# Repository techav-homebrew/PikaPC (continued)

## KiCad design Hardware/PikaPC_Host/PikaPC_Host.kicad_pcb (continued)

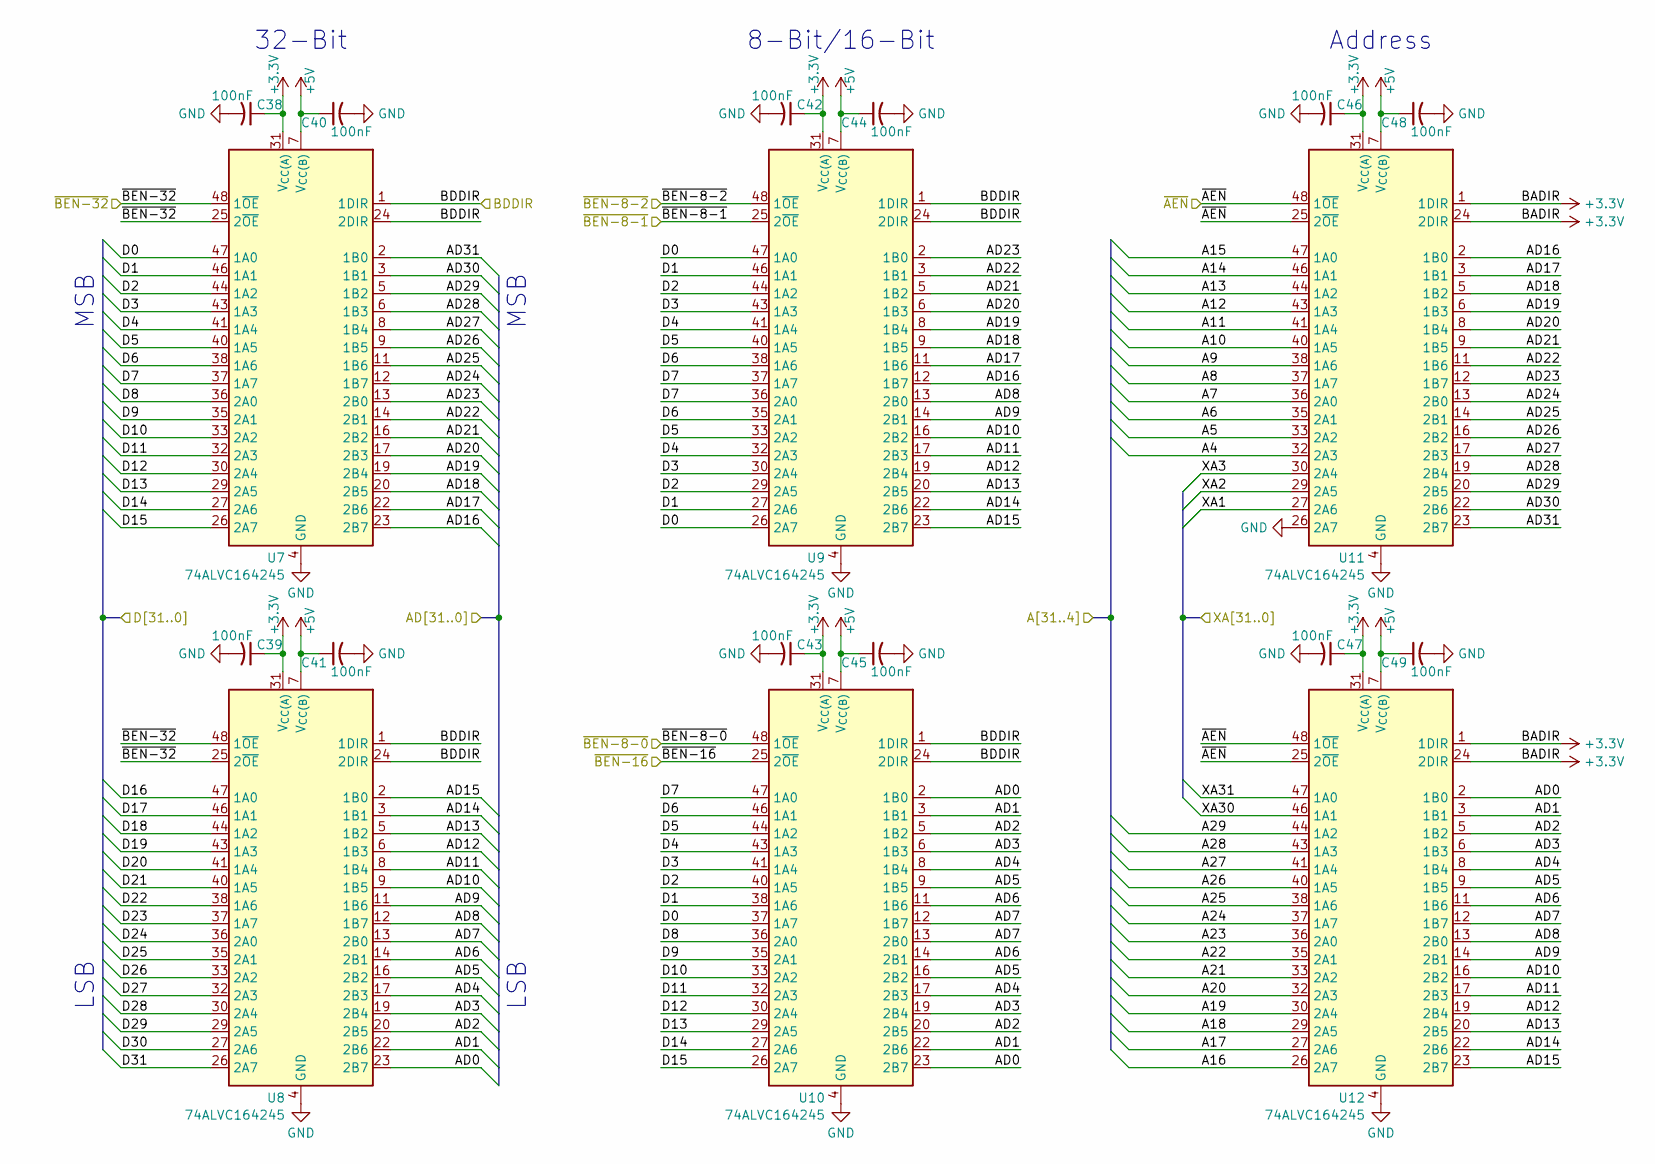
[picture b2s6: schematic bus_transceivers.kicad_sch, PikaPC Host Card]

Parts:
C38, C39, C40, C41, C42, C43, C44, C45, C46, C47, C48, C49: 100nF; C_0805_2012Metric; Mouser 187-CL21B104KACNNNC
U7, U8, U9, U10, U11, U12: 74ALVC164245; TSSOP-48_6.1x12.5mm_P0.5mm; Mouser 972-74ALVC164245PAG8

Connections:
+3.3V: C38.1, C39.1, C42.1, C43.1, C46.1, C47.1, U7.31 (V_{CC(A)}), U7.42 (V_{CC(A)}), U8.31 (V_{CC(A)}), U8.42 (V_{CC(A)}), U9.31 (V_{CC(A)}), U9.42 (V_{CC(A)}), U10.31 (V_{CC(A)}), U10.42 (V_{CC(A)}), U11.1 (1DIR), U11.24 (2DIR), U11.31 (V_{CC(A)}), U11.42 (V_{CC(A)}), U12.1 (1DIR), U12.24 (2DIR), U12.31 (V_{CC(A)}), U12.42 (V_{CC(A)}); also elsewhere on the board
+5V: C40.1, C41.1, C44.1, C45.1, C48.1, C49.1, U7.7 (V_{CC(B)}), U7.18 (V_{CC(B)}), U8.7 (V_{CC(B)}), U8.18 (V_{CC(B)}), U9.7 (V_{CC(B)}), U9.18 (V_{CC(B)}), U10.7 (V_{CC(B)}), U10.18 (V_{CC(B)}), U11.7 (V_{CC(B)}), U11.18 (V_{CC(B)}), U12.7 (V_{CC(B)}), U12.18 (V_{CC(B)}); also elsewhere on the board
/CPU Bus/D0: U7.47 (1A0), U9.26 (2A7), U9.47 (1A0), U10.37 (1A7); also elsewhere on the board
/CPU Bus/D1: U7.46 (1A1), U9.27 (2A6), U9.46 (1A1), U10.38 (1A6); also elsewhere on the board
/CPU Bus/D2: U7.44 (1A2), U9.29 (2A5), U9.44 (1A2), U10.40 (1A5); also elsewhere on the board
/CPU Bus/D3: U7.43 (1A3), U9.30 (2A4), U9.43 (1A3), U10.41 (1A4); also elsewhere on the board
/CPU Bus/D4: U7.41 (1A4), U9.32 (2A3), U9.41 (1A4), U10.43 (1A3); also elsewhere on the board
/CPU Bus/D5: U7.40 (1A5), U9.33 (2A2), U9.40 (1A5), U10.44 (1A2); also elsewhere on the board
/CPU Bus/D6: U7.38 (1A6), U9.35 (2A1), U9.38 (1A6), U10.46 (1A1); also elsewhere on the board
/CPU Bus/D7: U7.37 (1A7), U9.36 (2A0), U9.37 (1A7), U10.47 (1A0); also elsewhere on the board
/CPU Bus/D8: U7.36 (2A0), U10.36 (2A0); also elsewhere on the board
/CPU Bus/D9: U7.35 (2A1), U10.35 (2A1); also elsewhere on the board
/CPU Bus/D10: U7.33 (2A2), U10.33 (2A2); also elsewhere on the board
/CPU Bus/D11: U7.32 (2A3), U10.32 (2A3); also elsewhere on the board
/CPU Bus/D12: U7.30 (2A4), U10.30 (2A4); also elsewhere on the board
/CPU Bus/D13: U7.29 (2A5), U10.29 (2A5); also elsewhere on the board
/CPU Bus/D14: U7.27 (2A6), U10.27 (2A6); also elsewhere on the board
/CPU Bus/D15: U7.26 (2A7), U10.26 (2A7); also elsewhere on the board
/CPU Bus/D16: U8.47 (1A0); also elsewhere on the board
/CPU Bus/D17: U8.46 (1A1); also elsewhere on the board
/CPU Bus/D18: U8.44 (1A2); also elsewhere on the board
/CPU Bus/D19: U8.43 (1A3); also elsewhere on the board
/CPU Bus/D20: U8.41 (1A4); also elsewhere on the board
/CPU Bus/D21: U8.40 (1A5); also elsewhere on the board
/CPU Bus/D22: U8.38 (1A6); also elsewhere on the board
/CPU Bus/D23: U8.37 (1A7); also elsewhere on the board
/CPU Bus/D24: U8.36 (2A0); also elsewhere on the board
/CPU Bus/D25: U8.35 (2A1); also elsewhere on the board
/CPU Bus/D26: U8.33 (2A2); also elsewhere on the board
/CPU Bus/D27: U8.32 (2A3); also elsewhere on the board
/CPU Bus/D28: U8.30 (2A4); also elsewhere on the board
/CPU Bus/D29: U8.29 (2A5); also elsewhere on the board
/CPU Bus/D30: U8.27 (2A6); also elsewhere on the board
/CPU Bus/D31: U8.26 (2A7); also elsewhere on the board
/Main Bus/A6: U11.35 (2A1); also elsewhere on the board
/Main Bus/A7: U11.36 (2A0); also elsewhere on the board
/Main Bus/A8: U11.37 (1A7); also elsewhere on the board
/Main Bus/A9: U11.38 (1A6); also elsewhere on the board
/Main Bus/A10: U11.40 (1A5); also elsewhere on the board
/Main Bus/A11: U11.41 (1A4); also elsewhere on the board
/Main Bus/A12: U11.43 (1A3); also elsewhere on the board
/Main Bus/A13: U11.44 (1A2); also elsewhere on the board
/Main Bus/A14: U11.46 (1A1); also elsewhere on the board
/Main Bus/A15: U11.47 (1A0); also elsewhere on the board
/Main Bus/A16: U12.26 (2A7); also elsewhere on the board
/Main Bus/A17: U12.27 (2A6); also elsewhere on the board
/Main Bus/A18: U12.29 (2A5); also elsewhere on the board
/Main Bus/A19: U12.30 (2A4); also elsewhere on the board
/Main Bus/A20: U12.32 (2A3); also elsewhere on the board
/Main Bus/A21: U12.33 (2A2); also elsewhere on the board
/Main Bus/A22: U12.35 (2A1); also elsewhere on the board
/Main Bus/A23: U12.36 (2A0); also elsewhere on the board
/Main Bus/A24: U12.37 (1A7); also elsewhere on the board
/Main Bus/A25: U12.38 (1A6); also elsewhere on the board
/Main Bus/A26: U12.40 (1A5); also elsewhere on the board
/Main Bus/A27: U12.41 (1A4); also elsewhere on the board
/Main Bus/A28: U12.43 (1A3); also elsewhere on the board
/Main Bus/A29: U12.44 (1A2); also elsewhere on the board
/Main Bus/AD0: U8.23 (2B7), U10.2 (1B0), U10.23 (2B7), U12.2 (1B0); also elsewhere on the board
/Main Bus/AD1: U8.22 (2B6), U10.3 (1B1), U10.22 (2B6), U12.3 (1B1); also elsewhere on the board
/Main Bus/AD2: U8.20 (2B5), U10.5 (1B2), U10.20 (2B5), U12.5 (1B2); also elsewhere on the board
/Main Bus/AD3: U8.19 (2B4), U10.6 (1B3), U10.19 (2B4), U12.6 (1B3); also elsewhere on the board
/Main Bus/AD4: U8.17 (2B3), U10.8 (1B4), U10.17 (2B3), U12.8 (1B4); also elsewhere on the board
/Main Bus/AD5: U8.16 (2B2), U10.9 (1B5), U10.16 (2B2), U12.9 (1B5); also elsewhere on the board
/Main Bus/AD6: U8.14 (2B1), U10.11 (1B6), U10.14 (2B1), U12.11 (1B6); also elsewhere on the board
/Main Bus/AD7: U8.13 (2B0), U10.12 (1B7), U10.13 (2B0), U12.12 (1B7); also elsewhere on the board
/Main Bus/AD8: U8.12 (1B7), U9.13 (2B0), U12.13 (2B0); also elsewhere on the board
/Main Bus/AD9: U8.11 (1B6), U9.14 (2B1), U12.14 (2B1); also elsewhere on the board
/Main Bus/AD10: U8.9 (1B5), U9.16 (2B2), U12.16 (2B2); also elsewhere on the board
/Main Bus/AD11: U8.8 (1B4), U9.17 (2B3), U12.17 (2B3); also elsewhere on the board
/Main Bus/AD12: U8.6 (1B3), U9.19 (2B4), U12.19 (2B4); also elsewhere on the board
/Main Bus/AD13: U8.5 (1B2), U9.20 (2B5), U12.20 (2B5); also elsewhere on the board
/Main Bus/AD14: U8.3 (1B1), U9.22 (2B6), U12.22 (2B6); also elsewhere on the board
/Main Bus/AD15: U8.2 (1B0), U9.23 (2B7), U12.23 (2B7); also elsewhere on the board
/Main Bus/AD16: U7.23 (2B7), U9.12 (1B7), U11.2 (1B0); also elsewhere on the board
/Main Bus/AD17: U7.22 (2B6), U9.11 (1B6), U11.3 (1B1); also elsewhere on the board
/Main Bus/AD18: U7.20 (2B5), U9.9 (1B5), U11.5 (1B2); also elsewhere on the board
/Main Bus/AD19: U7.19 (2B4), U9.8 (1B4), U11.6 (1B3); also elsewhere on the board
/Main Bus/AD20: U7.17 (2B3), U9.6 (1B3), U11.8 (1B4); also elsewhere on the board
/Main Bus/AD21: U7.16 (2B2), U9.5 (1B2), U11.9 (1B5); also elsewhere on the board
/Main Bus/AD22: U7.14 (2B1), U9.3 (1B1), U11.11 (1B6); also elsewhere on the board
/Main Bus/AD23: U7.13 (2B0), U9.2 (1B0), U11.12 (1B7); also elsewhere on the board
/Main Bus/AD24: U7.12 (1B7), U11.13 (2B0); also elsewhere on the board
/Main Bus/AD25: U7.11 (1B6), U11.14 (2B1); also elsewhere on the board
/Main Bus/AD26: U7.9 (1B5), U11.16 (2B2); also elsewhere on the board
/Main Bus/AD27: U7.8 (1B4), U11.17 (2B3); also elsewhere on the board
/Main Bus/AD28: U7.6 (1B3), U11.19 (2B4); also elsewhere on the board
/Main Bus/AD29: U7.5 (1B2), U11.20 (2B5); also elsewhere on the board
/Main Bus/AD30: U7.3 (1B1), U11.22 (2B6); also elsewhere on the board
/Main Bus/AD31: U7.2 (1B0), U11.23 (2B7); also elsewhere on the board
/Main Bus/BDDIR: U7.1 (1DIR), U7.24 (2DIR), U8.1 (1DIR), U8.24 (2DIR), U9.1 (1DIR), U9.24 (2DIR), U10.1 (1DIR), U10.24 (2DIR); also elsewhere on the board
/Main Bus/XA1: U11.27 (2A6); also elsewhere on the board
/Main Bus/XA2: U11.29 (2A5); also elsewhere on the board
/Main Bus/XA3: U11.30 (2A4); also elsewhere on the board
/Main Bus/XA30: U12.46 (1A1); also elsewhere on the board
/Main Bus/XA31: U12.47 (1A0); also elsewhere on the board
/Main Bus/~AEN: U11.25 (2~OE), U11.48 (1~OE), U12.25 (2~OE), U12.48 (1~OE); also elsewhere on the board
/Main Bus/~BEN-8-0: U10.48 (1~OE); also elsewhere on the board
/Main Bus/~BEN-8-1: U9.25 (2~OE); also elsewhere on the board
/Main Bus/~BEN-8-2: U9.48 (1~OE); also elsewhere on the board
/Main Bus/~BEN-16: U10.25 (2~OE); also elsewhere on the board
/Main Bus/~BEN-32: U7.25 (2~OE), U7.48 (1~OE), U8.25 (2~OE), U8.48 (1~OE); also elsewhere on the board

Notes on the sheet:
LSB
MSB
8-Bit/16-Bit
Address
32-Bit

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
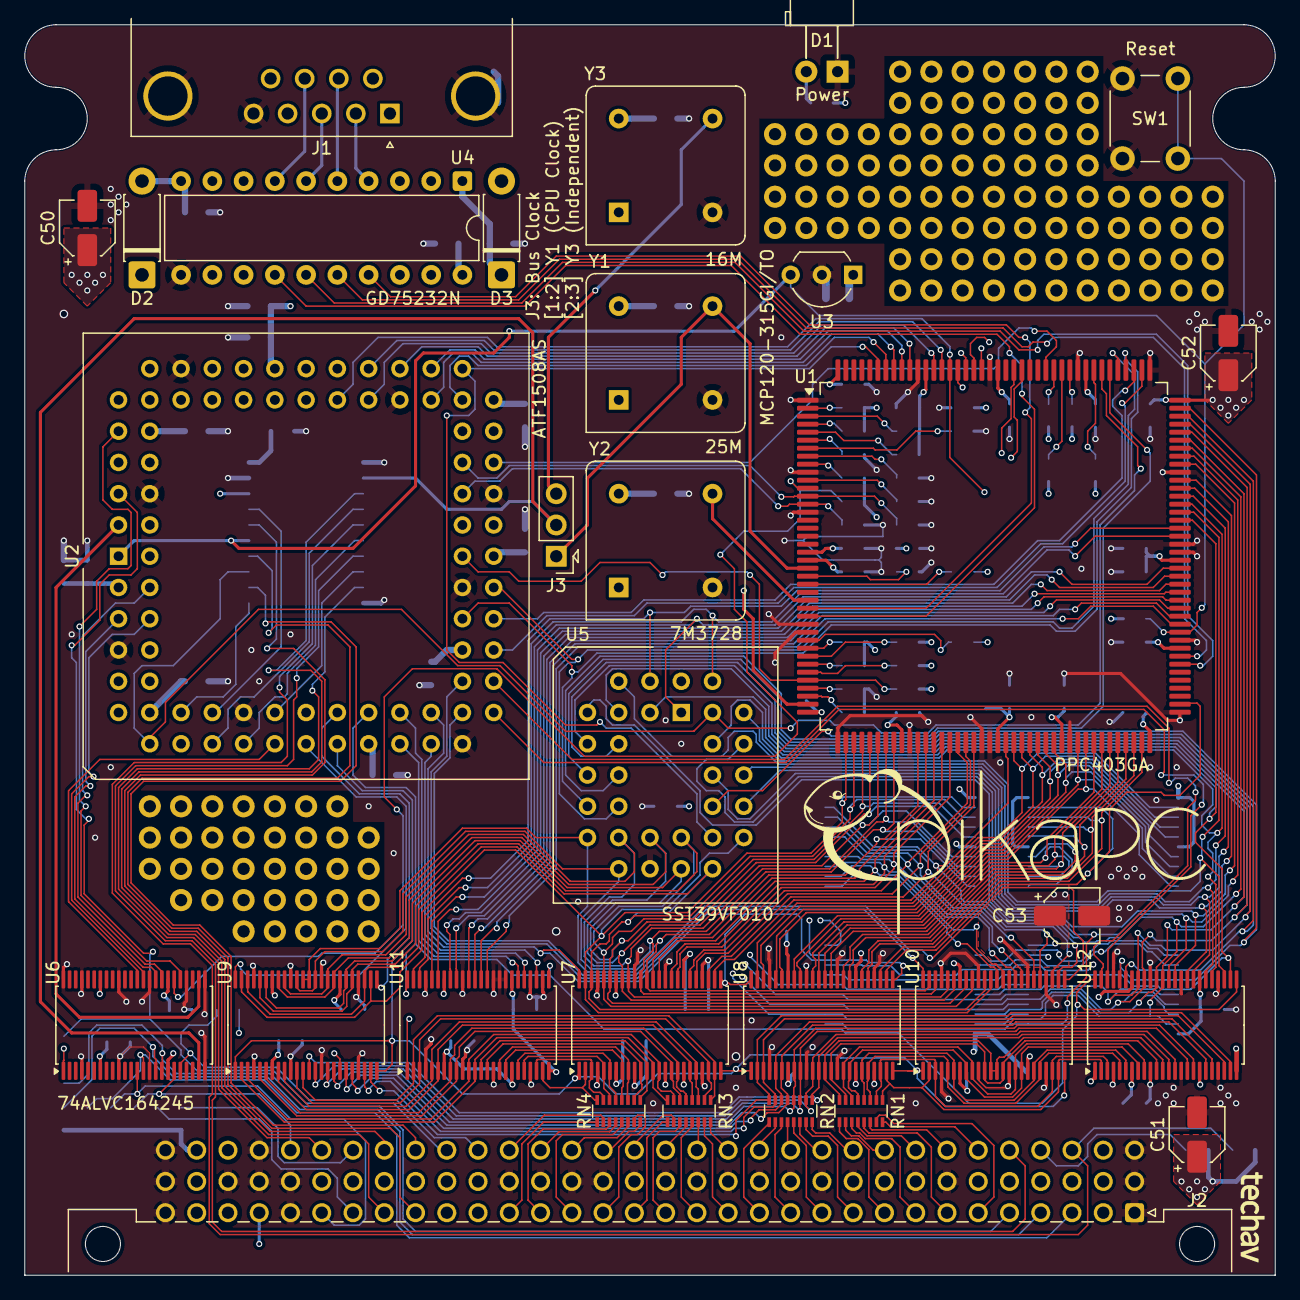
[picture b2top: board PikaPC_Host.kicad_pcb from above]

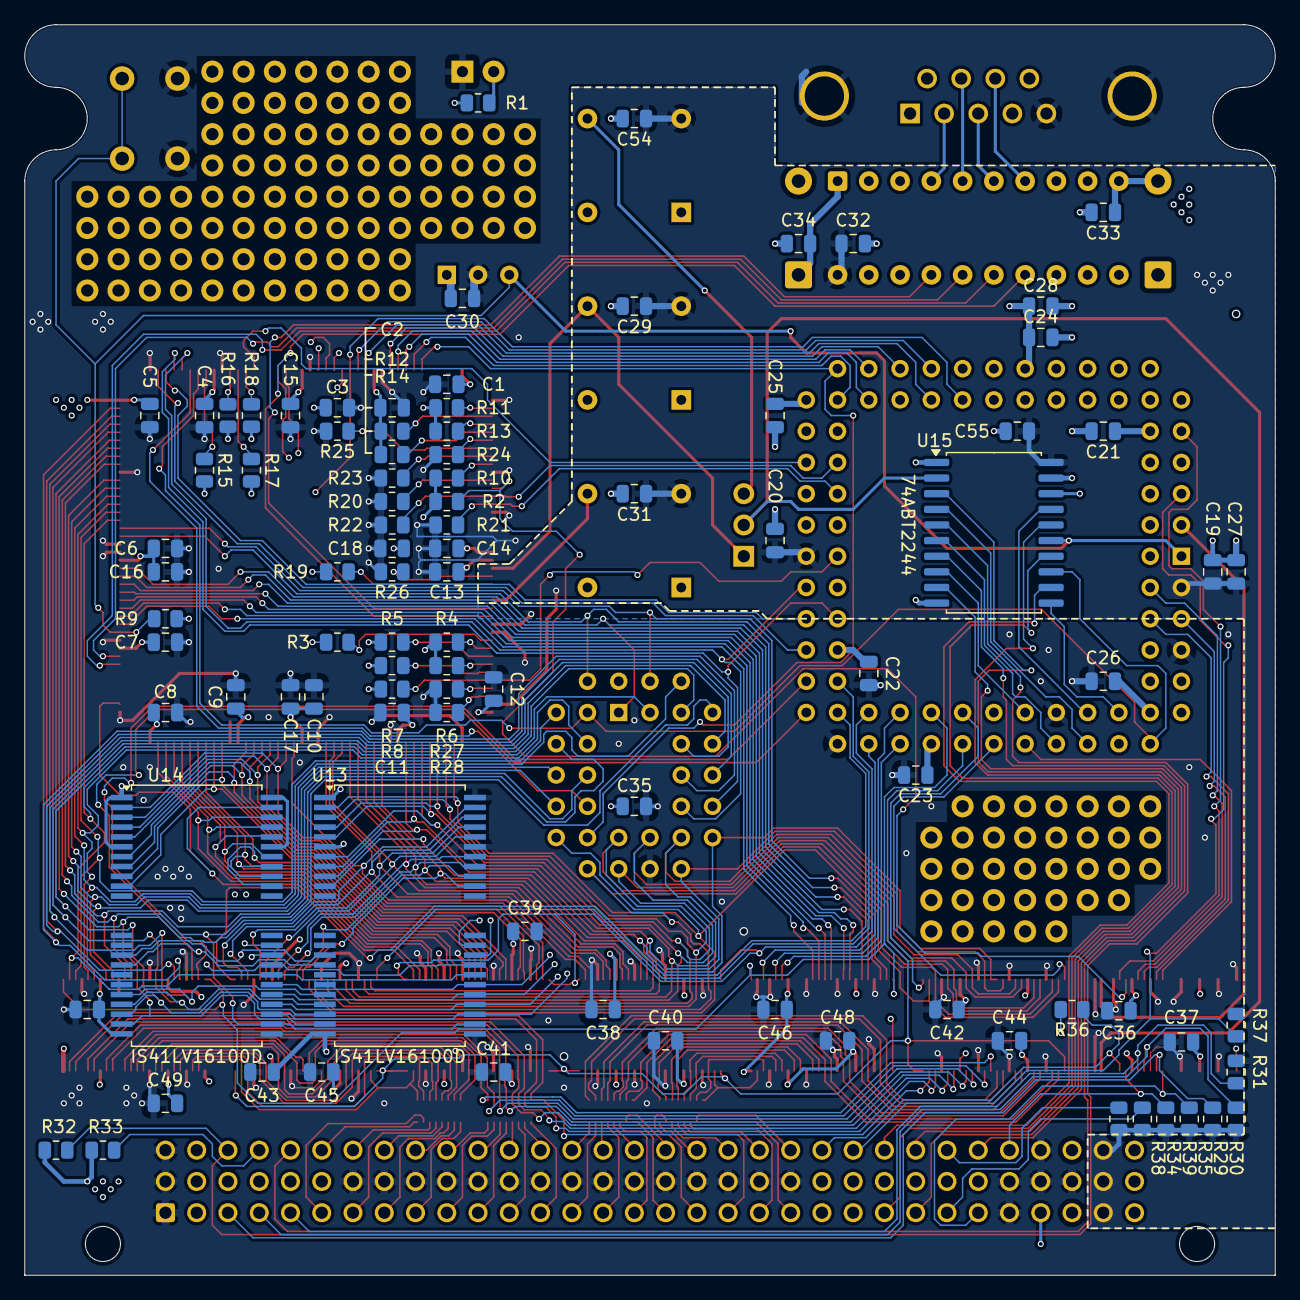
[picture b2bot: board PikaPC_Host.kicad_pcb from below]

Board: 4 copper layers, 101.6 x 101.6 mm, 123 parts (93 on the bottom side), 229 nets.

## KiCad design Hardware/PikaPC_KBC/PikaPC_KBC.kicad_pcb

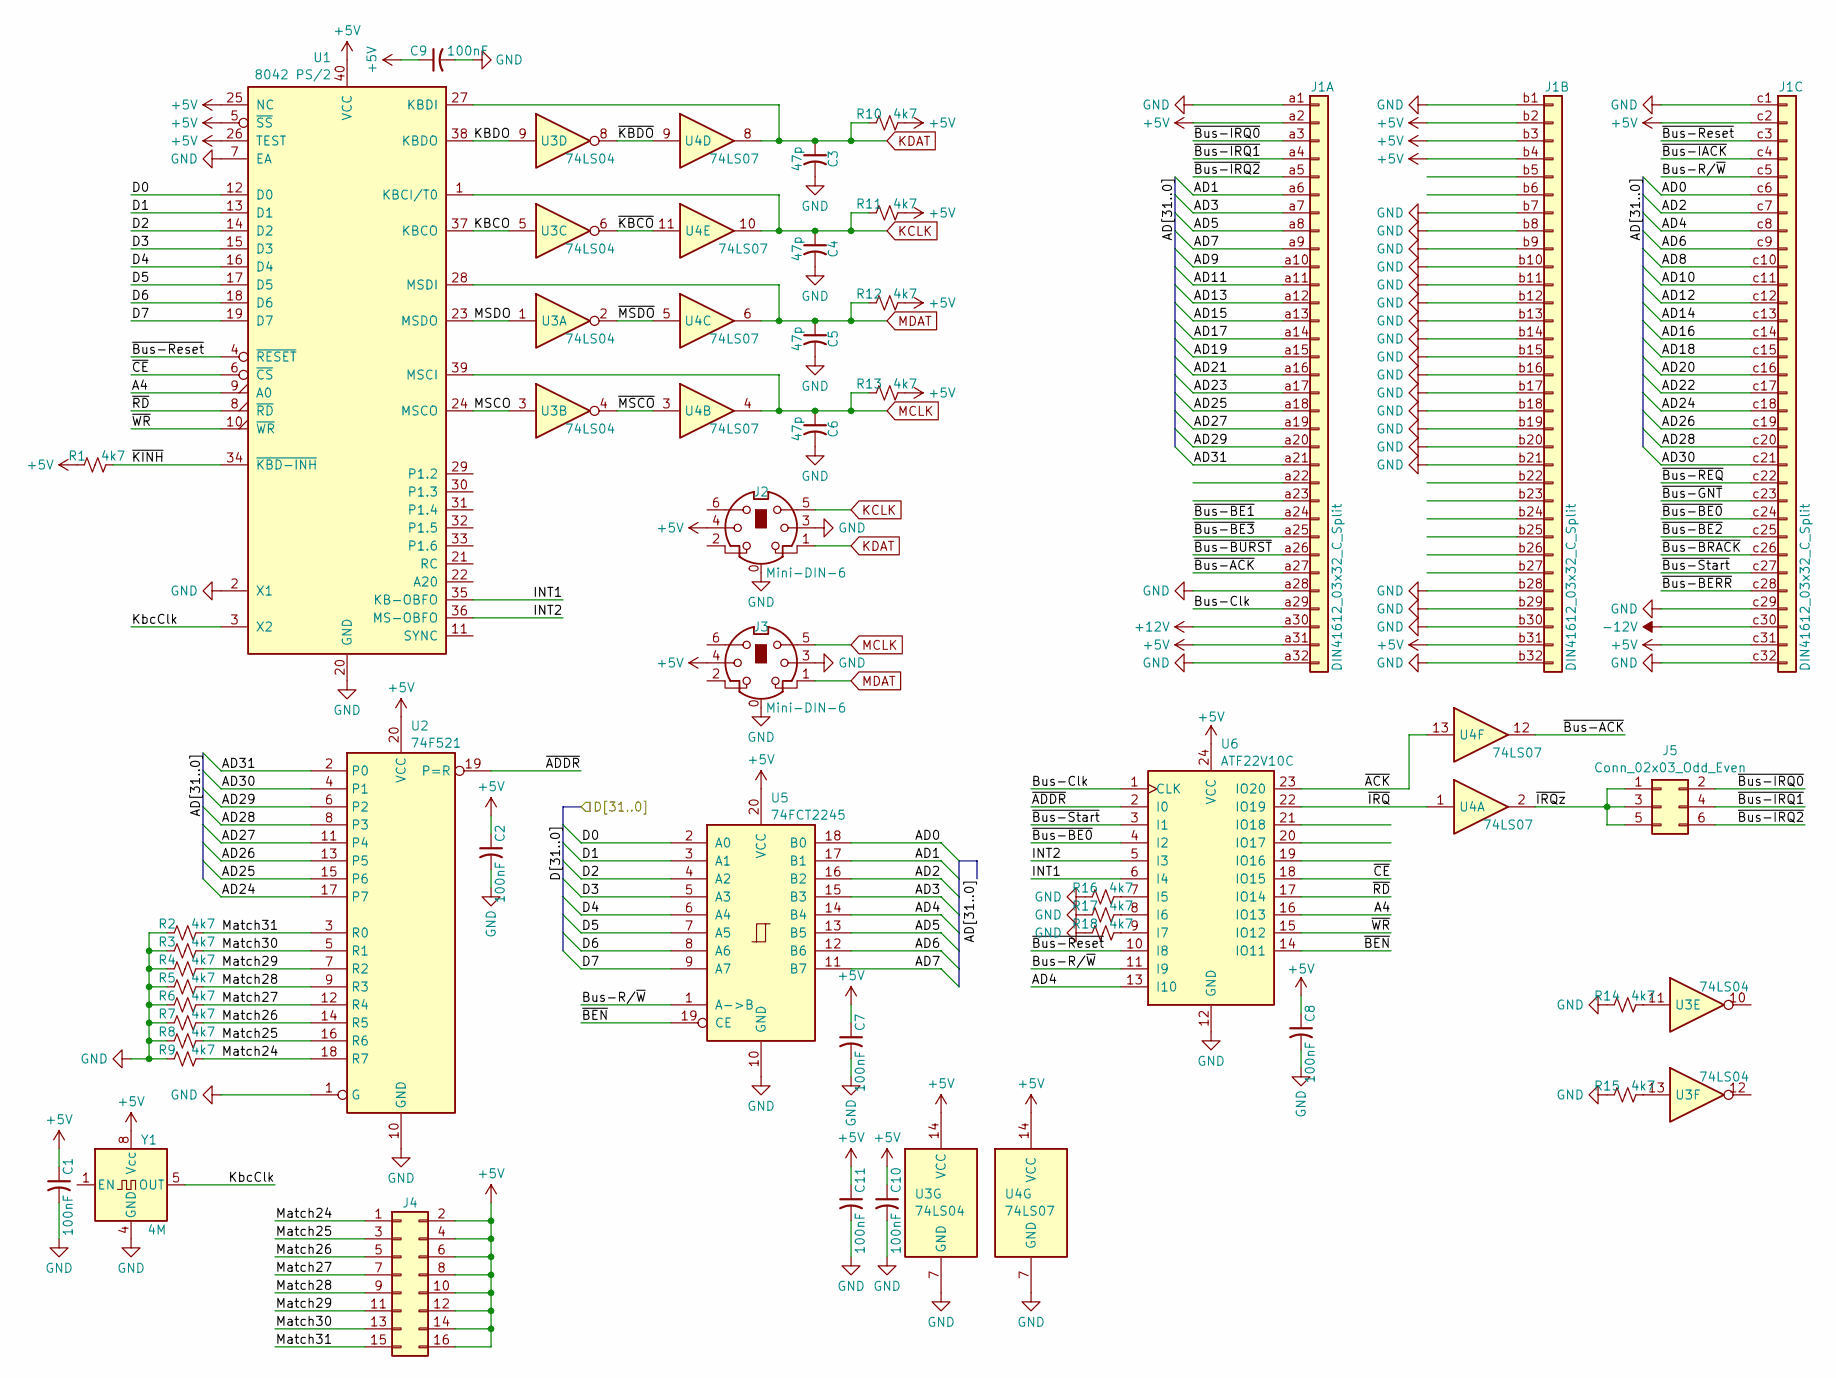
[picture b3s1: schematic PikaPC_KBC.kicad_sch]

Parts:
C1, C2, C7, C8, C9, C10, C11: 100nF; C_0805_2012Metric; Mouser 187-CL21B104KACNNNC
C3, C4, C5, C6: 47p; C_Disc_D3.0mm_W2.0mm_P2.50mm; Mouser 810-FG18C0G1H470JNT6
J1: DIN41612_03x32_C_Split; DIN41612_C_3x32_Male_Horizontal_THT
J2, J3: Mini-DIN-6; MiniDIN6
J4: Conn_02x08_Odd_Even; PinHeader_2x08_P2.54mm_Vertical
J5: Conn_02x03_Odd_Even; PinHeader_2x03_P2.54mm_Vertical
R1, R2, R3, R4, R5, R6, R7, R8, R9, R10, R11, R12, R13, R14, R15, R16, R17, R18: 4k7; R_0805_2012Metric; Mouser 303-0805W8J0472T5E
U1: 8042 PS/2; DIP-40_W15.24mm_Socket
U2: 74F521; SOIC-20W_7.5x12.8mm_P1.27mm; Mouser 595-SN74F521DWR
U3: 74LS04; DIP-14_W7.62mm_Socket; Mouser 595-SN74LS04N
U4: 74LS07; DIP-14_W7.62mm_Socket; Mouser 595-SN74LS07N
U5: 74FCT2245; SOIC-20W_7.5x12.8mm_P1.27mm; Mouser 595-CY74FCT2245TSOCT
U6: ATF22V10C; DIP-24_W7.62mm_Socket; Mouser 556-ATF22V10C-10PU
Y1: 4M; Oscillator_DIP-8

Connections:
+5V: C1.1, C2.1, C7.1, C8.1, C9.1, C10.1, C11.1, J1.a2, J1.a31, J1.b2, J1.b3, J1.b4, J1.b31, J1.c2, J1.c31, J2.4, J3.4, J4.2, J4.4, J4.6, J4.8, J4.10, J4.12, J4.14, J4.16, R1.1, R10.2, R11.2, R12.2, R13.2, U1.5 (~SS), U1.25 (NC), U1.26 (TEST), U1.40 (VCC), U2.20 (VCC), U3.14 (VCC), U4.14 (VCC), U5.20 (VCC), U6.24 (VCC), Y1.8 (Vcc)
+12V: J1.a30
-12V: J1.c30
/A4: U1.9 (A0), U6.16 (IO13)
/AD0: J1.c6, U5.18 (B0)
/AD1: J1.a6, U5.17 (B1)
/AD2: J1.c7, U5.16 (B2)
/AD3: J1.a7, U5.15 (B3)
/AD4: J1.c8, U5.14 (B4), U6.13 (I10)
/AD5: J1.a8, U5.13 (B5)
/AD6: J1.c9, U5.12 (B6)
/AD7: J1.a9, U5.11 (B7)
/AD8: J1.c10
/AD9: J1.a10
/AD10: J1.c11
/AD11: J1.a11
/AD12: J1.c12
/AD13: J1.a12
/AD14: J1.c13
/AD15: J1.a13
/AD16: J1.c14
/AD17: J1.a14
/AD18: J1.c15
/AD19: J1.a15
/AD20: J1.c16
/AD21: J1.a16
/AD22: J1.c17
/AD23: J1.a17
/AD24: J1.c18, U2.17 (P7)
/AD25: J1.a18, U2.15 (P6)
/AD26: J1.c19, U2.13 (P5)
/AD27: J1.a19, U2.11 (P4)
/AD28: J1.c20, U2.8 (P3)
/AD29: J1.a20, U2.6 (P2)
/AD30: J1.c21, U2.4 (P1)
/AD31: J1.a21, U2.2 (P0)
/Bus-Clk: J1.a29, U6.1 (CLK)
/Bus-R/~W: J1.c5, U5.1 (A->B), U6.11 (I9)
/D0: U1.12 (D0), U5.2 (A0)
/D1: U1.13 (D1), U5.3 (A1)
/D2: U1.14 (D2), U5.4 (A2)
/D3: U1.15 (D3), U5.5 (A3)
/D4: U1.16 (D4), U5.6 (A4)
/D5: U1.17 (D5), U5.7 (A5)
/D6: U1.18 (D6), U5.8 (A6)
/D7: U1.19 (D7), U5.9 (A7)
/INT1: U1.35 (KB-OBFO), U6.6 (I4)
/INT2: U1.36 (MS-OBFO), U6.5 (I3)
/KBCO: U1.37 (KBCO), U3.5
/KBDO: U1.38 (KBDO), U3.9
/KbcClk: U1.3 (X2), Y1.5 (OUT)
/MSCO: U1.24 (MSCO), U3.3
/MSDO: U1.23 (MSDO), U3.1
/Match24: J4.1, R9.2, U2.18 (R7)
/Match25: J4.3, R8.2, U2.16 (R6)
/Match26: J4.5, R7.2, U2.14 (R5)
/Match27: J4.7, R6.2, U2.12 (R4)
/Match28: J4.9, R5.2, U2.9 (R3)
/Match29: J4.11, R4.2, U2.7 (R2)
/Match30: J4.13, R3.2, U2.5 (R1)
/Match31: J4.15, R2.2, U2.3 (R0)
/~ACK: U4.13, U6.23 (IO20)
/~ADDR: U2.19 (P=R), U6.2 (I0)
/~BEN: U5.19 (CE), U6.14 (IO11)
/~Bus-ACK: J1.a27, U4.12
/~Bus-BE0: J1.c24, U6.4 (I2)
/~Bus-BE1: J1.a24
/~Bus-BE2: J1.c25
/~Bus-BE3: J1.a25
/~Bus-BERR: J1.c28
/~Bus-BRACK: J1.c26
/~Bus-BURST: J1.a26
/~Bus-GNT: J1.c23
/~Bus-IACK: J1.c4
/~Bus-IRQ0: J1.a3, J5.2
/~Bus-IRQ1: J1.a4, J5.4
/~Bus-IRQ2: J1.a5, J5.6
/~Bus-REQ: J1.c22
/~Bus-Reset: J1.c3, U1.4 (~RESET), U6.10 (I8)
/~Bus-Start: J1.c27, U6.3 (I1)
/~CE: U1.6 (~CS), U6.18 (IO15)
/~IRQz: J5.1, J5.3, J5.5, U4.2
/~IRQ: U4.1, U6.22 (IO19)
/~KBCO: U3.6, U4.11
/~KBDO: U3.8, U4.9
/~KINH: R1.2, U1.34 (~KBD-INH)
/~MSCO: U3.4, U4.3
/~MSDO: U3.2, U4.5
/~RD: U1.8 (~RD), U6.17 (IO14)
/~WR: U1.10 (~WR), U6.15 (IO12)
GND: C1.2, C2.2, C3.2, C4.2, C5.2, C6.2, C7.2, C8.2, C9.2, C10.2, C11.2, J1.a1, J1.a28, J1.a32, J1.b1, J1.b7, J1.b8, J1.b9, J1.b10, J1.b11, J1.b12, J1.b13, J1.b14, J1.b15, J1.b16, J1.b17, J1.b18, J1.b19, J1.b20, J1.b21, J1.b28, J1.b29, J1.b30, J1.b32, J1.c1, J1.c29, J1.c32, J2.0, J2.3, J3.0, J3.3, R2.1, R3.1, R4.1, R5.1, R6.1, R7.1, R8.1, R9.1, R14.1, R15.1, R16.1, R17.1, R18.1, U1.2 (X1), U1.7 (EA), U1.20 (GND), U2.1 (G), U2.10 (GND), U3.7 (GND), U4.7 (GND), U5.10 (GND), U6.12 (GND), Y1.4 (GND)
KCLK: C4.1, J2.5, R11.1, U1.1 (KBCI/T0), U4.10
KDAT: C3.1, J2.1, R10.1, U1.27 (KBDI), U4.8
MCLK: C6.1, J3.5, R13.1, U1.39 (MSCI), U4.4
MDAT: C5.1, J3.1, R12.1, U1.28 (MSDI), U4.6
unnamed: R14.2, U3.11
unnamed: R15.2, U3.13
unnamed: R16.2, U6.7 (I5)
unnamed: R17.2, U6.8 (I6)
unnamed: R18.2, U6.9 (I7)

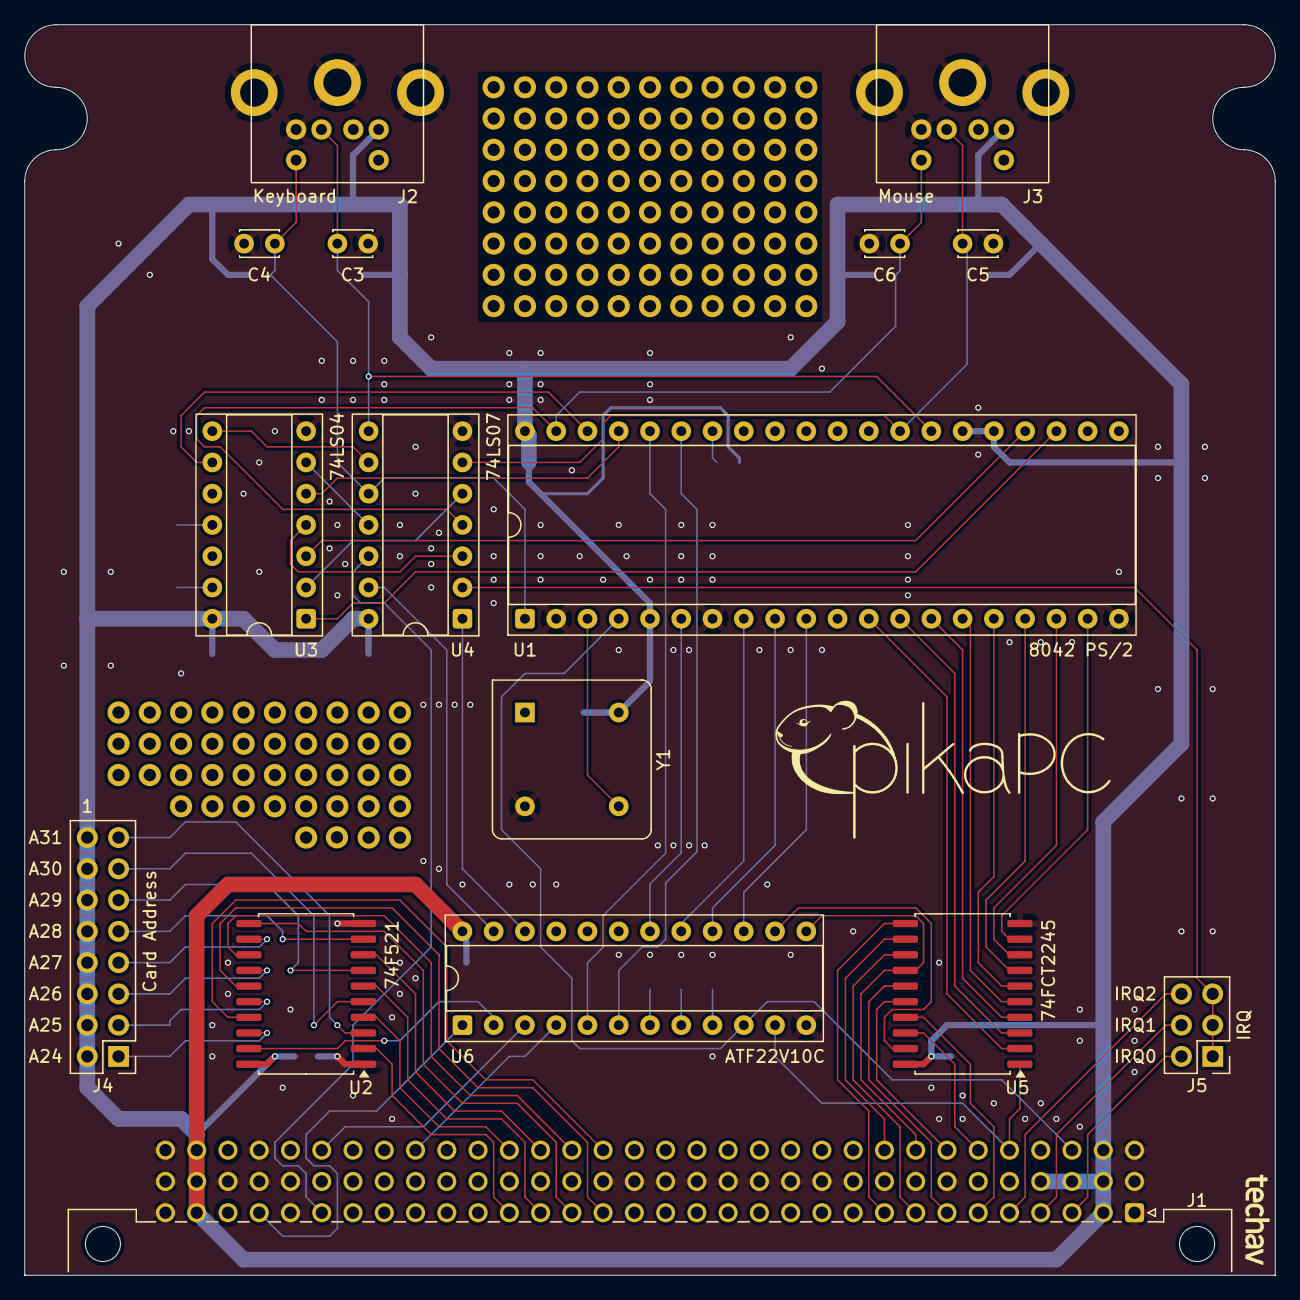
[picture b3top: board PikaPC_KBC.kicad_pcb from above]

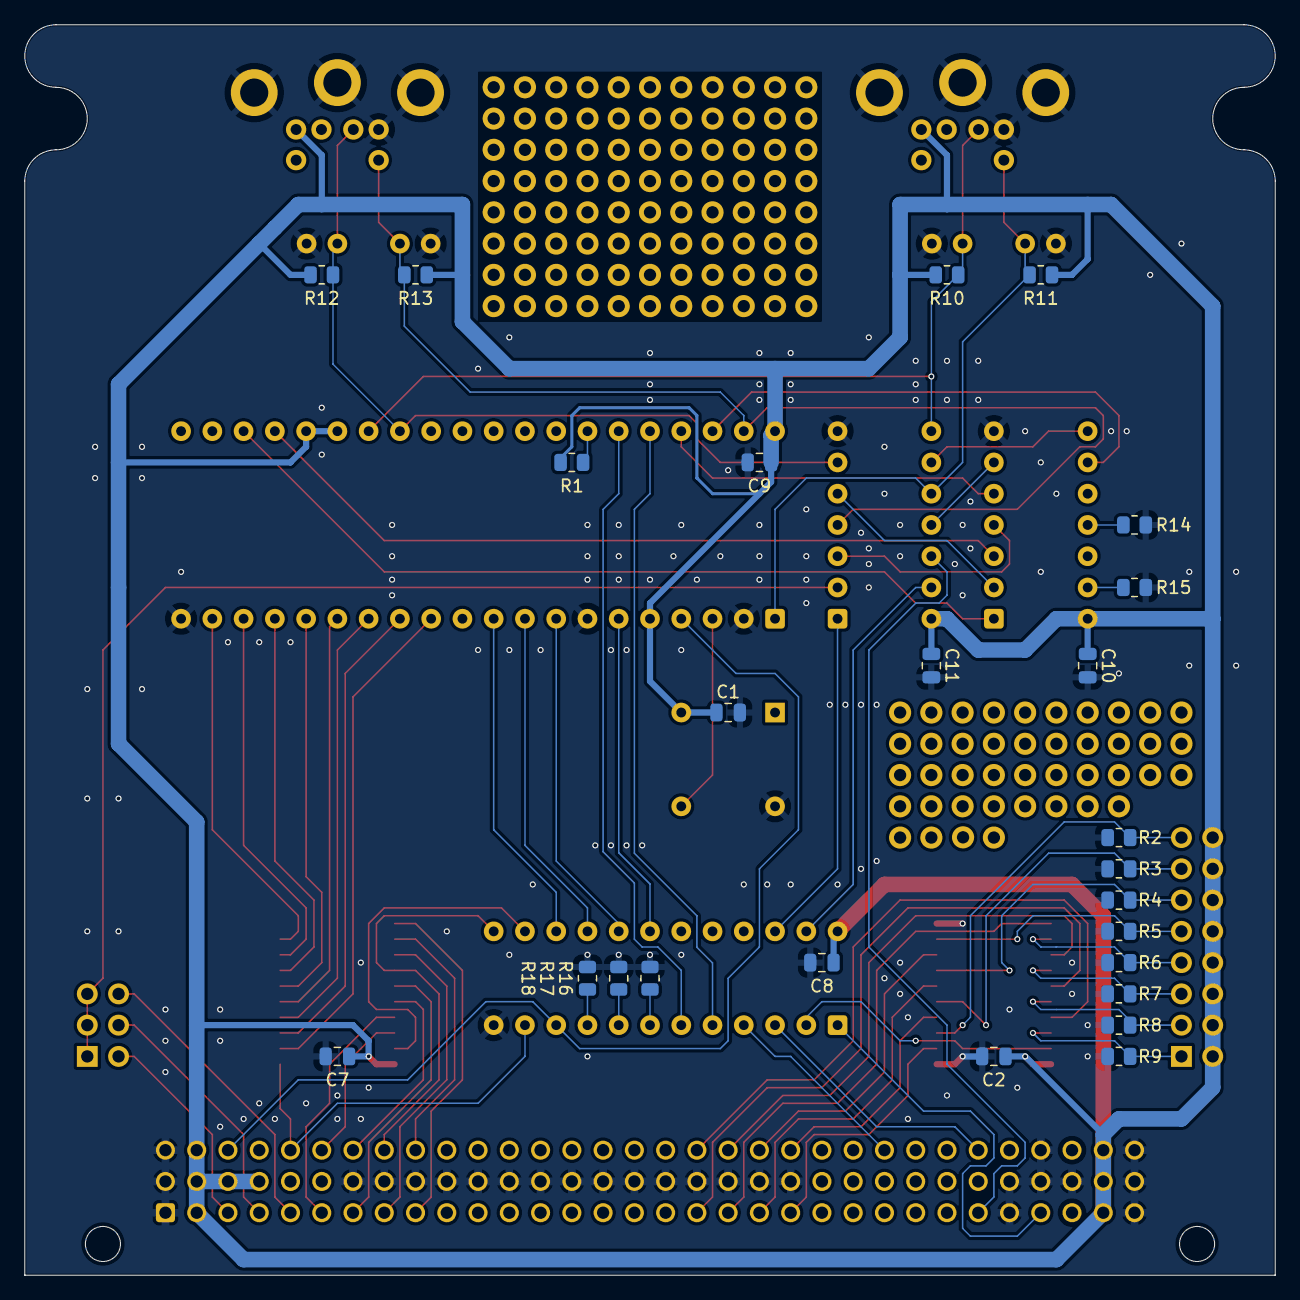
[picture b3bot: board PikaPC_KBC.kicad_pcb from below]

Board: 2 copper layers, 101.6 x 101.6 mm, 41 parts (25 on the bottom side), 73 nets.

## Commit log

2025-10-05 Initialize Repo
2025-10-05 Add gitignore, logo
2025-10-05 Initial schematic draft
2025-10-05 Add Battraw PPCForth
2025-10-05 Change from 72-pin SIMM to SRAM
2025-10-05 Add Utilities & attribution to gitignore
2025-10-06 initial compile for 403ga
    - change target CPU
    - add conditions for dictionary keywords relying on features no present on 403ga
    - fix incorrectly-formatted comment in local.inc that was preventing successful compile
    - add windows powershell compile script
    - add compiler output files to gitignore
2025-10-08 Rename write strobes
2025-10-12 Platform-specific changes
    - update rom/ram size
    - update bank register & iocr initialization
    - update baud rate settings
2025-10-13 Add condition for LED I/O not present on 403ga
2025-10-13 use 5V signalling for Rx & CTS
2025-10-15 A few simple Forth demos
    hellorld.fth
    - it's a classic
    leo_numbers.fth
    - calculates first 100 Leonardo & Fibonacci numbers
    mandelbrot.fth
    - simple integer ASCII Mandelbrot fractal renderer
2025-10-18 Format documentation for printing
2025-10-30 Add 8042 PS/2 Keyboard/Mouse controller
2025-10-31 Keyboard/Mouse controller use '04/'07
    - use tried & true 7404+7407 instead of discrete transistors
2025-11-02 Add vS3 ViRGE video & SD interface
2025-11-04 Peripheral Bus Control logic
    - ATF22V10C control logic for 5V peripheral bus
2025-11-08 cleanup keyboard logic
    - odds & ends found while wiring
2025-11-08 Invert system clock to ViRGE
2025-11-09 Debug peripheral bus controller logic
    - fix `PDBEN`/`PBDEN` typo
    - SBEx should always be qualified by PBDEN
2025-11-09 Set up bank registers for new peripherals
2025-12-07 ViRGE schematic/layout cleanup
2025-12-07 keyboard controller test program
2025-12-07 ViRGE Strapping pulldowns should be on VMD not PD
2025-12-08 VGA output use full-size header, add ferrite beads
2025-12-08 add wincupl output files to gitignore
2025-12-15 Troubleshooting ViRGE communication
    - use A[25:23] for ViRGE SAUP[2:1] & M/IO# signals
    - add pull-up resistors to ViRGE ready & loca signals
    - adjust bank registers for new memory map
    - add forth test program for VGA init & ID
2025-12-17 ViRGE byte select fixes
    - swap data bus byte order
    - decode low address bits for write byte selects
2025-12-17 ViRGE byte select fixes 2
    - swap byte select output order on bus control logic
    - update VGA initialization forth program
2025-12-28 New peripheral bus
    - additional bus transceivers for byte lane steering to VLB
    - replace 22V10 with 1504 for peripheral bus control logic
2026-01-03 New peripheral bus debugging
    - add pull-ups to bus transceiver enable signals for debugging
    - change reset pull-up to 1k to help with rise times
    - update bank registers configuration for new peripheral bus
2026-01-04 New peripheral bus control debugging
    - delay VLB ReadyIn on read cycles, sync to clock on write cycles
    - fix 32-bit VLB byte enable signals
2026-01-05 VRAM control debugging
    - add strapping resistors for slow vram cycles
    - fix swapped CAS2 & CAS3 pins on ViRGE symbol
2026-01-25 VRAM control debugging
    - correct clock edge for VLB ReadyIn
    - minor tweaks for S3 ViRGE symbol
    - add series resistors to VRAM control signals
    - add strapping resistor to support Trio64V+
2026-01-27 Add VGA test routines
2026-01-27 update gitignore
2026-01-28 Start Host card
    initial schematic, start board layout
2026-01-30 Host card PCB layout
2026-01-31 Rework bus pinout
2026-02-01 72-pin SIMM Card
    schematic & PCB layout
2026-02-01 ViRGE video card initial schematic
2026-02-02 ViRGE card start PCB layout
2026-02-03 ViRGE card PCB layout
2026-02-04 Host Card refinement
    add main bus clock selection
    silkscreen cleanup
2026-02-05 Rework Host Card bus clock
    add optional separate bus oscillator
2026-02-05 Power & Bus Termination card
2026-02-07 Add Keyboard Controller card
2026-02-07 Un-assign main bus pins 22 & 23
2026-02-07 Silkscreen cleanup
2026-02-11 Annotate & prep for output - Host & KBC
    add gerber output to gitignore
2026-02-15 Prep for output
2026-02-15 Add IDE interface card
2026-02-28 Add prototyping card
2026-03-07 BoM updates
2026-03-07 Add new bus to wire-wrap mainboard
2026-03-24 new bus control logic
2026-03-25 bus control timing fixes
    - correct sWAIT state to actually wait for ACKn signal
    - force state machine to idle if CSn[7..0] do not indicate active cycle
    - use falling edge of active cycle to reset STARTn immediately at end of cycle
    - assert byte enable signals during address state and through termination state
2026-03-29 SIMM72 card logic
2026-04-01 ViRGE card logic
2026-04-01 Modifications for host card vs prototype
2026-04-03 fix low two expansion bus address bits
2026-04-03 add missing pull-ups on SRDY# & RDYIN#
2026-04-03 Assert ADS# on falling edge & reset state on START# rising edge
2026-04-04 Add pull-up to LOCA# on ViRGE card
2026-04-08 Fix output enable strobe on ViRGE card
2026-04-08 Add video mandelbrot forth demo
2026-04-11 update forth examples
2026-04-11 start C integer mandelbrot example
2026-04-12 VGA initialization in C
2026-04-12 add minimal linker script
2026-04-12 graphics mode (13h) initialization
    not quite working, but it's close
2026-04-12 Working mandelbrot using soft float
2026-04-13 zooming mandelbrot demo; start converting to fixed-point
2026-04-14 fixed-point C mandelbrot
2026-04-19 add pull-down resistors to AD bus
2026-04-19 Initialize Trio for 15bpp
2026-04-20 fix memory pointers, bank 1 configuration
2026-04-20 don't double-buffer bus clock, add missing bus control signal pull-ups
2026-04-23 video mandelbrot better zoom demo
2026-04-25 video mandelbrot better zoom demo render target level
2026-05-01 Remove redundant SIP resistor from mainboard
2026-05-01 Add mini bus card
2026-05-01 Host Card updates
    - add missing bus pull-ups
    - add on-board DRAM
    - add series termination resistors to AD bus
    - fix DE9 footprint mounting hole location
    - fix double-buffered bus clock
    - use 74'2244 buffer w/series term resistors for bus control signals
2026-05-01 Fix vga initialization for vMandelbrot
2026-05-02 Add 2MB SRAM card
2026-05-03 updates for gerber output
2026-05-06 add proper makefile for vMandelbrot
2026-05-19 SRAM Card logic
2026-05-24 Update ppcforth addresses for rev2 host card main memory
    - currently non-functional because exception handlers cannot branch from
    vector table in RAM to routines in ROM.
2026-05-24 Host card should not route A4/A5 to expansion bus
2026-05-24 Use CS7 for host RAM cycles
2026-05-24 copy rom to ram on startup
    - avoids problems with out-of-range branches from exception vectors
2026-05-24 update vmandelbrot address to new host memory map
2026-05-25 re-enable cache for ppcforth
2026-05-26 Add startup banner
2026-05-26 Initial KBC card logic
